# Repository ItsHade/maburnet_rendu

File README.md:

### *BOM*
| Reference | Quantity | Value | Footprint |
| --- | --- | --- | --- |
| C1, C2 | 2 | 12pF | maburnet:C SMD |
| C3, C4, C7 | 3 | 100nF | maburnet:C SMD |
| C6 | 1 | 1uF | maburnet:C SMD |
| D1 | 1 | Green | maburnet: LED Green |
| D2 | 1 | Red | maburnet: LED Red |
| J1 | 1 | | maburnet:J1 THT |
| J2 | 1 | | maburnet:J2 THT |
| J3 | 1 | | maburnet:J3 THT |
| R1 | 1 | 330 | maburnet:R SMD |
| R2, R3 | 2 | 10K | maburnet:R SMD |
| SW1 | 1 | SW_Push | maburnet:Switch SMD |
| U1 | 1 | ATmega328P-A | maburnet:ATMEGA328P-AU |
| Y1 | 1 | Crystal Oscillator 9pF | maburnet:Crystal SMD |

### *PINOUT*
|Module      |   ATMEGA328P |
|------------|:------------:|
[J3]         |       |
|GND         |   GND |
|GND         |   GND |
|5V          |   VCC |
|TX          |   PD1 (TXO) |
|RX          |   PD0 (RXI) |
|DTR         |   PC6 |
|[J2]        |       |
|+           |   VCC |
|-           |   GND |
|RST         |   PC6 (RESET) |
|5V          |   VCC |
|A3          |   PC3 |
|A2          |   PC2 |
|A1          |   PC1 |
|A0          |   PC0 |
|D13         |   PB5 (SCK) |
|D12         |   PB4 (MISO) |
|D11         |   PB3 (MOSI) |
|D10         |   PB2 |
|[J1]        |       |
|D9          |   PB1 |
|D8          |   PB0 |
|D7          |   PD7 |
|D6          |   PD6 |
|D5          |   PD5 |
|D4          |   PD4 |
|D3          |   PD3 |
|D2          |   PD2 |
|GND         |   GND |
|RST         |   PC6 |
|<           |   PD0 |
|>           |   PD1 |

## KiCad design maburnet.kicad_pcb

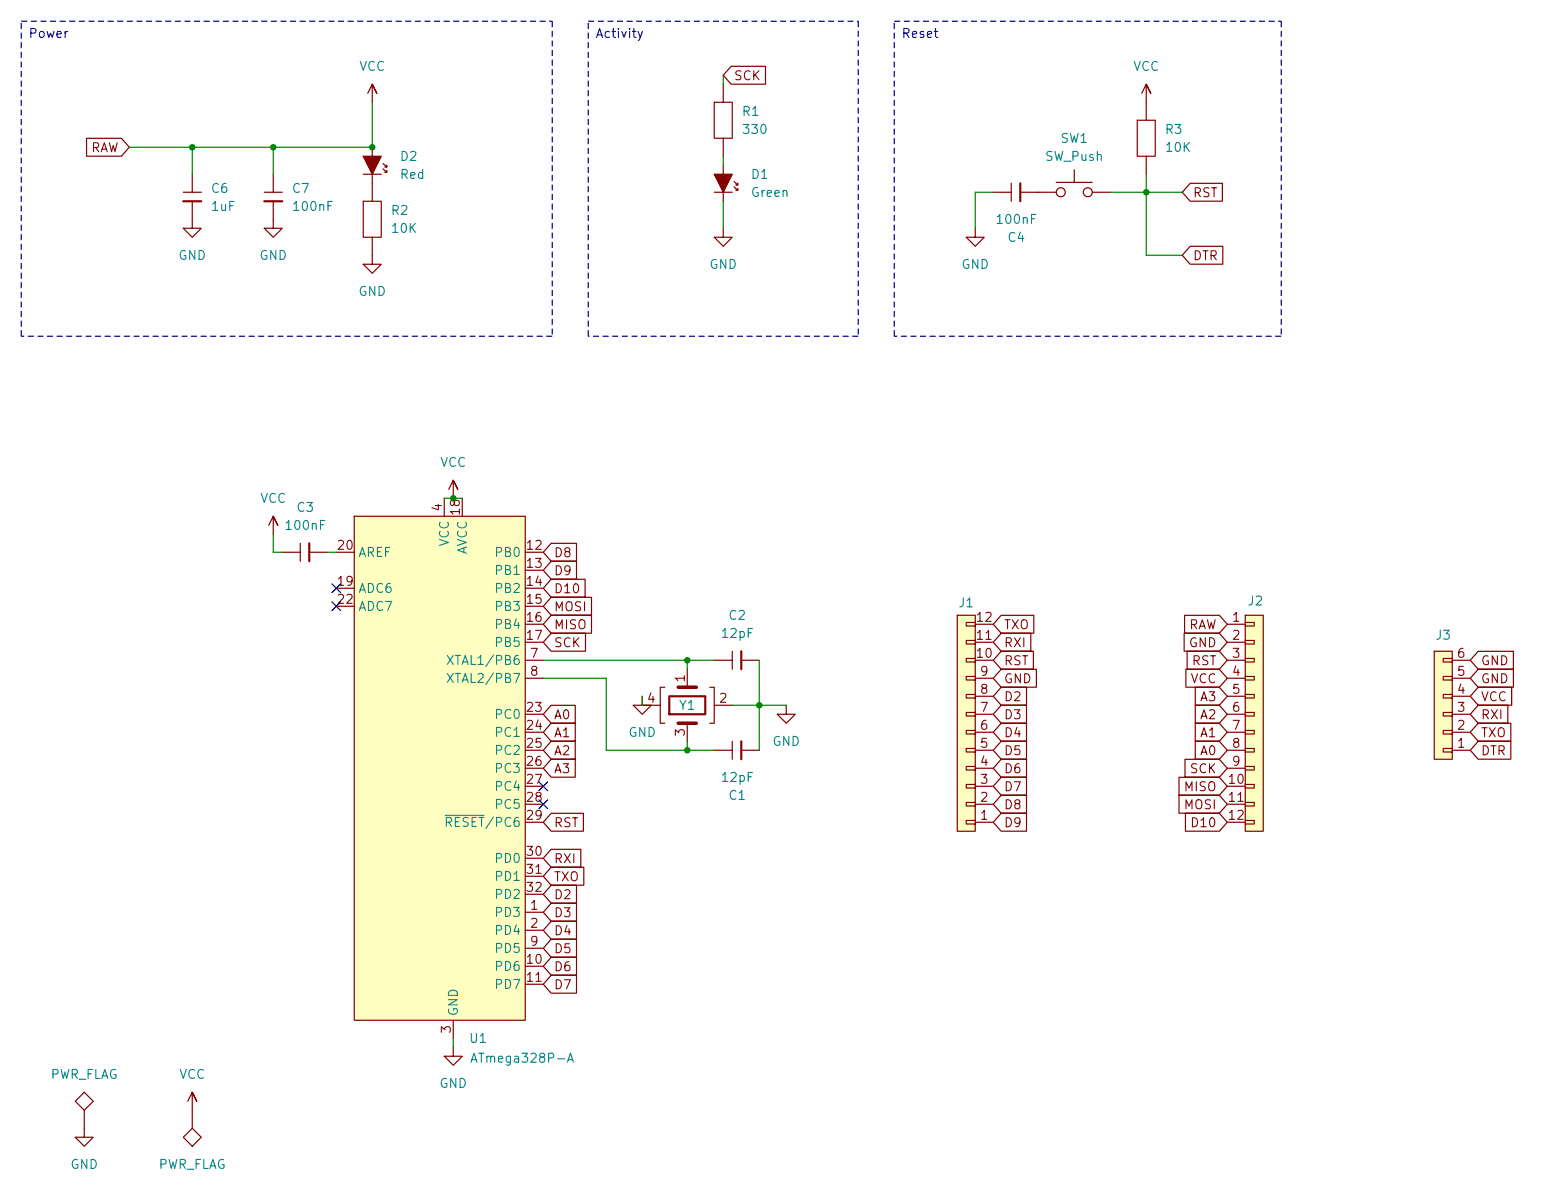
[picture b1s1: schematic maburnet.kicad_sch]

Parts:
C1, C2: 12pF; C SMD
C3, C4, C7: 100nF; C SMD
C6: 1uF; C SMD
D1: Green; LED Green SMD
D2: Red; LED Red SMD
J1: J1 THT
J2: J2 THT
J3: J3 THT
R1: 330; R SMD
R2, R3: 10K; R SMD
SW1: SW_Push; Switch SMD
U1: ATmega328P-A; ATMEGA328P-AU
Y1: Crystal SMD

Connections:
A0: J2.8, U1.23 (PC0)
A1: J2.7, U1.24 (PC1)
A2: J2.6, U1.25 (PC2)
A3: J2.5, U1.26 (PC3)
D2: J1.8, U1.32 (PD2)
D3: J1.7, U1.1 (PD3)
D4: J1.6, U1.2 (PD4)
D5: J1.5, U1.9 (PD5)
D6: J1.4, U1.10 (PD6)
D7: J1.3, U1.11 (PD7)
D8: J1.2, U1.12 (PB0)
D9: J1.1, U1.13 (PB1)
D10: J2.12, U1.14 (PB2)
DTR: J1.10, J2.3, J3.1, R3.2, SW1.2, U1.29 (~RESET/PC6)
MISO: J2.10, U1.16 (PB4)
MOSI: J2.11, U1.15 (PB3)
unnamed: C4.2, SW1.1
unnamed: D1.1, R1.2
unnamed: D2.2, R2.1
unnamed: C3.2, U1.20 (AREF)
unnamed: C2.1, U1.7 (XTAL1/PB6), Y1.1
unnamed: C1.1, U1.8 (XTAL2/PB7), Y1.3
RXI: J1.11, J3.3, U1.30 (PD0)
SCK: J2.9, R1.1, U1.17 (PB5)
TXO: J1.12, J3.2, U1.31 (PD1)

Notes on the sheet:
Reset
Activity
Power

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
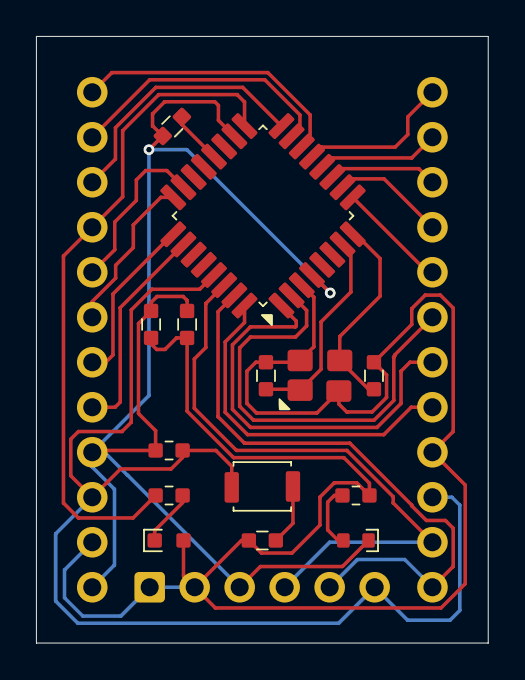
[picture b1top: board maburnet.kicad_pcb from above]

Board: 2 copper layers, 25.1 x 33.7 mm, 17 parts (0 on the bottom side), 27 nets.

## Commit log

2025-11-24 rendu
2025-11-24 lib tables
2025-11-24 final
